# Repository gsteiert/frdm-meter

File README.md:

# frdm-meter
Voltage &amp; Current Meter AFE for FRDM boards

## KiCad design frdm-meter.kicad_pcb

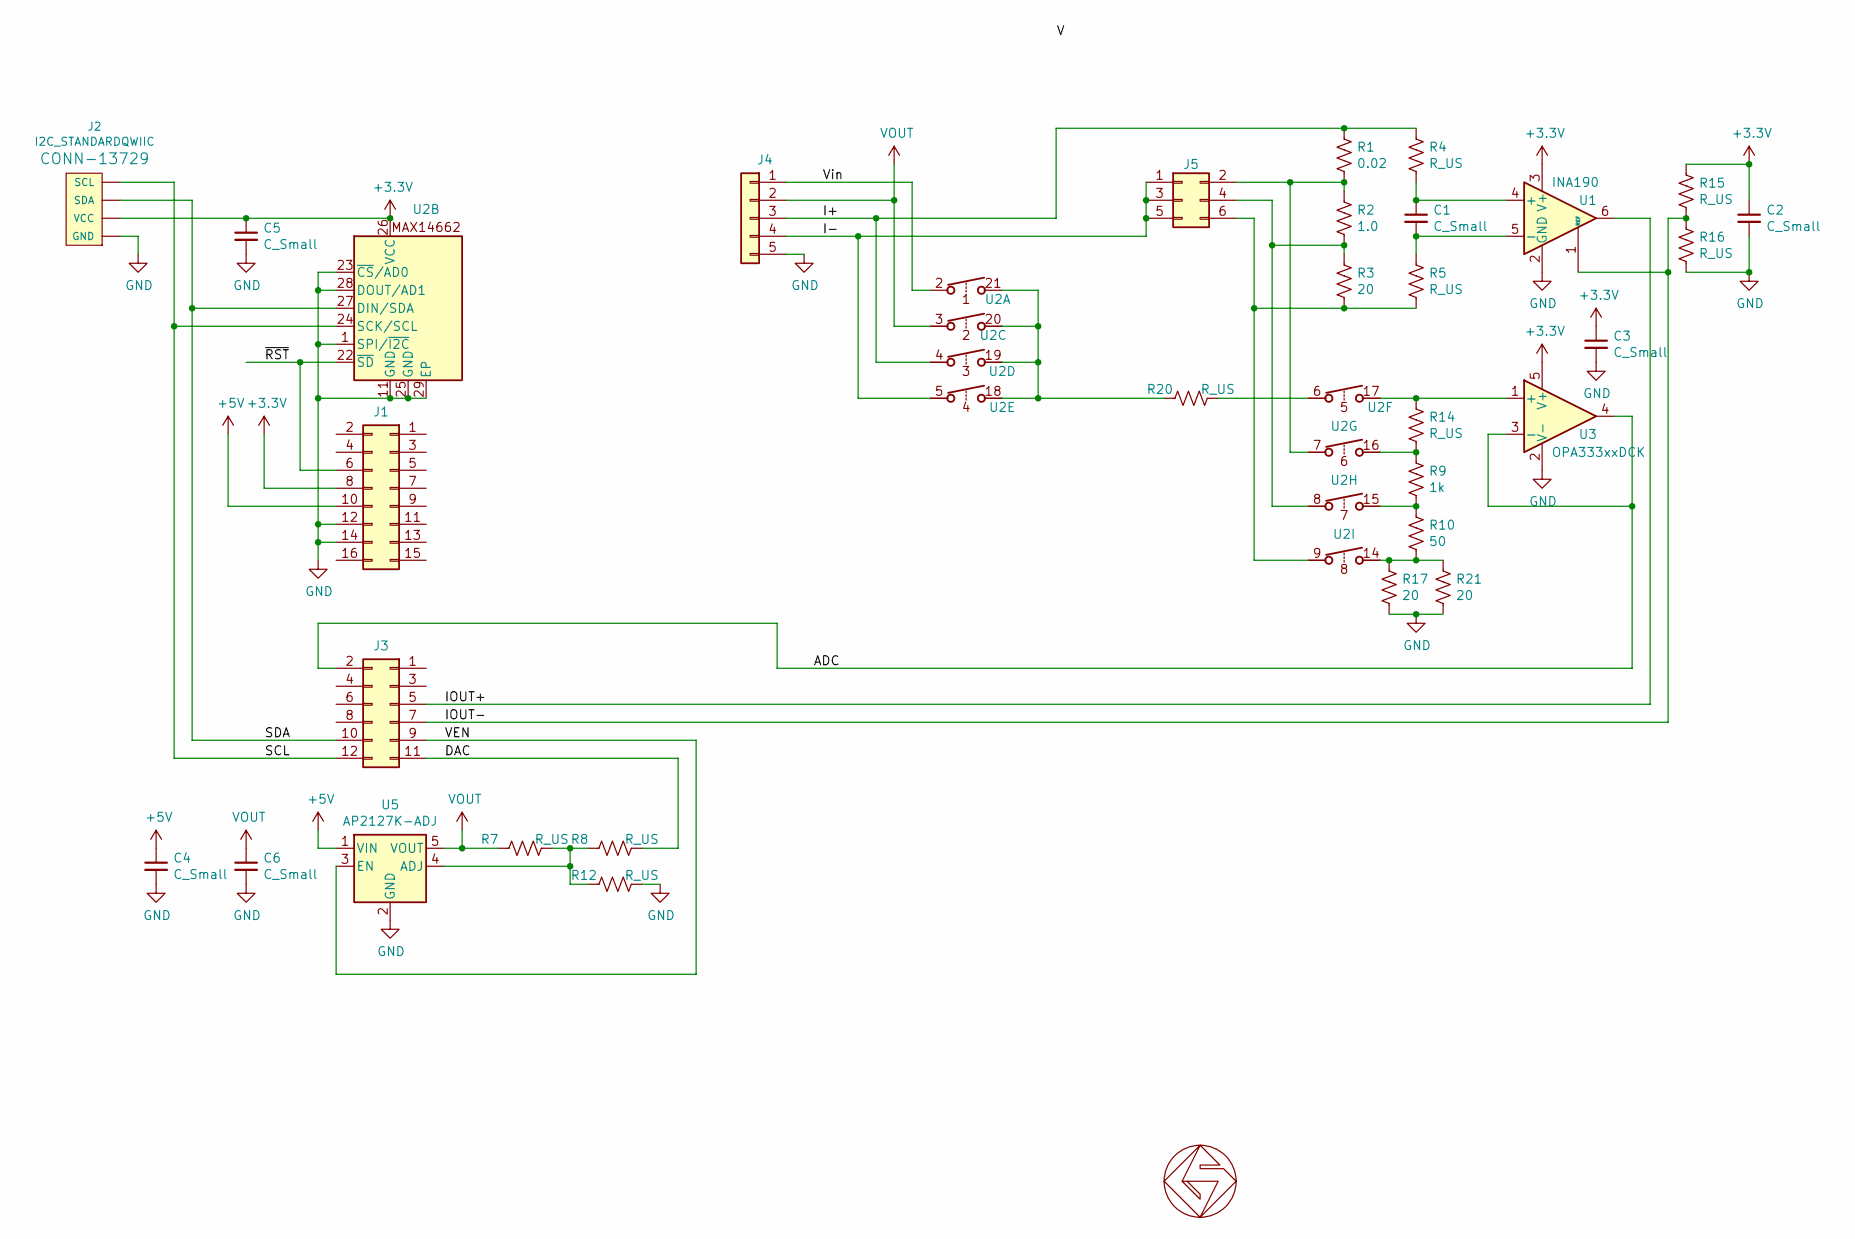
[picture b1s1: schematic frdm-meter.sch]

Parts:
C1, C2: C_Small; C_0603_1608Metric
C3, C4, C5, C6: C_Small; C_0603_1608Metric_Pad1.05x0.95mm_HandSolder
GS1: GS_logo; gs_logo_200mil
J1: Conn_02x08_Odd_Even; PinHeader_2x08_P2.54mm_Vertical_SMD
J2: I2C_STANDARDQWIIC; JST_SH_SM04B-SRSS-TB_1x04-1MP_P1.00mm_Horizontal
J3: Conn_02x06_Odd_Even; PinHeader_2x06_P2.54mm_Vertical_SMD
J4: Conn_01x05; PinHeader_1x05_P2.54mm_Vertical
J5: Conn_02x03_Odd_Even; PinHeader_2x03_P2.54mm_Vertical_SMD
R1: 0.02; R_0603_1608Metric
R2: 1.0; R_0603_1608Metric
R3, R17, R21: 20; R_0603_1608Metric
R4, R5, R7, R8, R12, R14, R15, R16, R20: R_US; R_0603_1608Metric
R9: 1k; R_0603_1608Metric
R10: 50; R_0603_1608Metric
U1: INA190; SOT-363_SC-70-6
U2: MAX14662; QFN-28-1EP_4x4mm_P0.4mm_EP2.6x2.6mm
U3: OPA333xxDCK; SOT-353_SC-70-5
U5: AP2127K-ADJ; SOT-23-5

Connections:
+3V3: C2.1, C3.1, C5.1, J1.8, J2.2 (VCC), R15.1, U1.3 (V+), U2.26 (VCC), U3.5 (V+)
+5V: C4.1, J1.10, U5.1 (VIN)
/ADC: J3.2, U3.3 (-), U3.4
/DAC: J3.11, R8.1
/I+: J4.3, R1.1, R4.1, U2.4
/I-: J4.4, J5.1, J5.3, J5.5, U2.5
/IOUT+: J3.5, U1.6
/IOUT-: J3.7, R15.2, R16.1, U1.1 (REF)
/SCL: J2.4 (SCL), J3.12, U2.24 (SCK/SCL)
/SDA: J2.3 (SDA), J3.10, U2.27 (DIN/SDA)
/VEN: J3.9, U5.3 (EN)
/Vin: J4.1, U2.2
/~RST~: J1.6, U2.22 (~SD~)
GND: C2.2, C3.2, C4.2, C5.2, C6.2, J1.12, J1.14, J2.1 (GND), J4.5, R12.1, R16.2, R17.2, R21.2, U1.2 (GND), U2.1 (SPI/~I2C~), U2.11 (GND), U2.23 (~CS~/AD0), U2.25 (GND), U2.28 (DOUT/AD1), U2.29 (EP), U3.2 (V-), U5.2 (GND)
unnamed: C1.1, R4.2, U1.4 (+)
unnamed: C1.2, R5.1, U1.5 (-)
unnamed: J5.2, R1.2, R2.1, U2.7
unnamed: J5.4, R2.2, R3.1, U2.8
unnamed: J5.6, R3.2, R5.2, U2.9
unnamed: R9.2, R10.1, U2.15
unnamed: R10.2, R17.1, R21.1, U2.14
unnamed: R7.1, R8.2, R12.2, U5.4 (ADJ)
unnamed: R14.1, U2.17, U3.1 (+)
unnamed: R9.1, R14.2, U2.16
unnamed: R20.1, U2.6
unnamed: R20.2, U2.18, U2.19, U2.20, U2.21
VDC: C6.1, J4.2, R7.2, U2.3, U5.5 (VOUT)

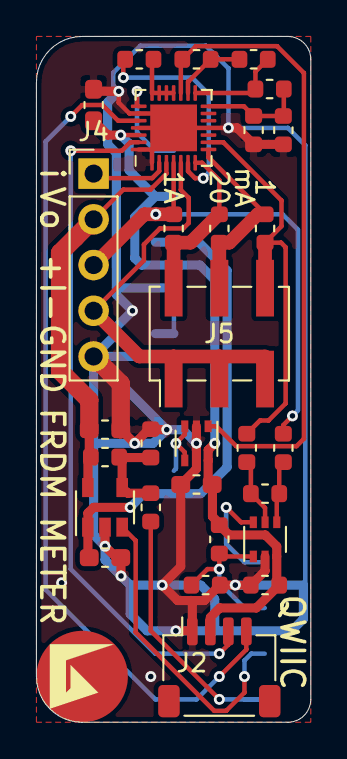
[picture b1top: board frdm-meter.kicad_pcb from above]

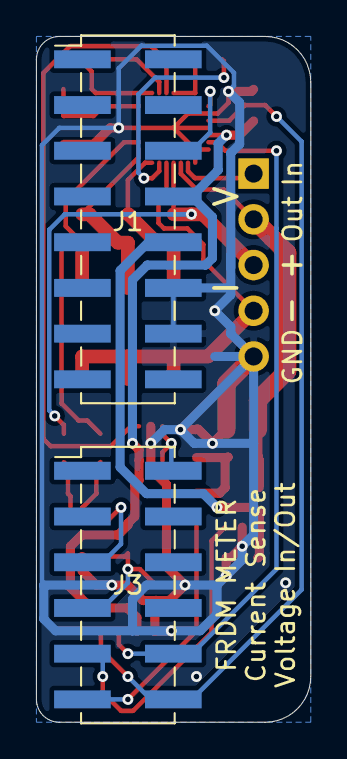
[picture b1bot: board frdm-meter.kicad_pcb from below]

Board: 2 copper layers, 15.2 x 38.1 mm, 32 parts (2 on the bottom side), 27 nets.

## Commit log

2020-11-10 adding design files
